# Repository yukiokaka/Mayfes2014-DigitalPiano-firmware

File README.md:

Mayfes2014-DigitalPiano-firmware
================================

This repository includes the firmware of DigitalPiano, made for mayfes 2014, EEIC the Universiy of Tokyo

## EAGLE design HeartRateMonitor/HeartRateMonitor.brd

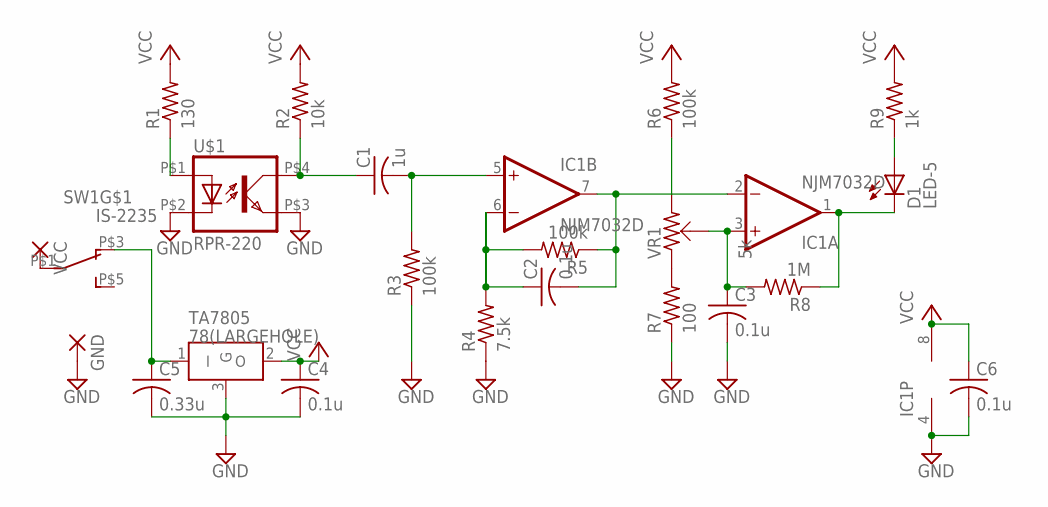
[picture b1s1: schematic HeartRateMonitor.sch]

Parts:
C1: 1u; C050-024X044
C2, C3, C4, C6: 0.1u; C050-024X044
C5: 0.33u; C050-024X044
D1: LED-5; LED5
GND: POWERPAD-2.4
IC1: NJM7032D; DIL08
R1: 130; 0207/10
R2: 10k; 0207/10
R3, R5, R6: 100k; 0207/10
R4: 7.5k; 0207/10
R7: 100; 0207/10
R8: 1M; 0207/10
R9: 1k; 0207/10
SW1: IS-2235
TA7805: 78(LARGEHOLE); 7805-LARGEHOLE
U$1: RPR-220
VCC: POWERPAD-2.4
VR1: 5k; VR-637A

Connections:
GND: C3.2, C4.2, C5.2, C6.2, GND.1, IC1.4 (V-), R3.1, R4.1, R7.1, TA7805.3 (G), U$1.P$2 (C), U$1.P$3 (EMIT)
unnamed: R1.1, U$1.P$1 (A)
unnamed: C1.1, R2.1, U$1.P$4 (COL)
unnamed: C1.2, IC1.5 (+IN), R3.2
unnamed: D1.A, R9.1
unnamed: C2.1, IC1.6 (-IN), R4.2, R5.2
unnamed: C2.2, IC1.2 (-IN), IC1.7 (OUT), R5.1
unnamed: R7.2, VR1.1
unnamed: R6.1, VR1.2
unnamed: C3.1, IC1.3 (+IN), R8.2, VR1.BR
unnamed: C5.1, SW1.P$3 (O), TA7805.1 (I)
unnamed: D1.K, IC1.1 (OUT), R8.1
unnamed: SW1.P$1, VCC.1
VCC: C4.1, C6.1, IC1.8 (V+), R1.2, R2.2, R6.2, R9.2, TA7805.2 (O)

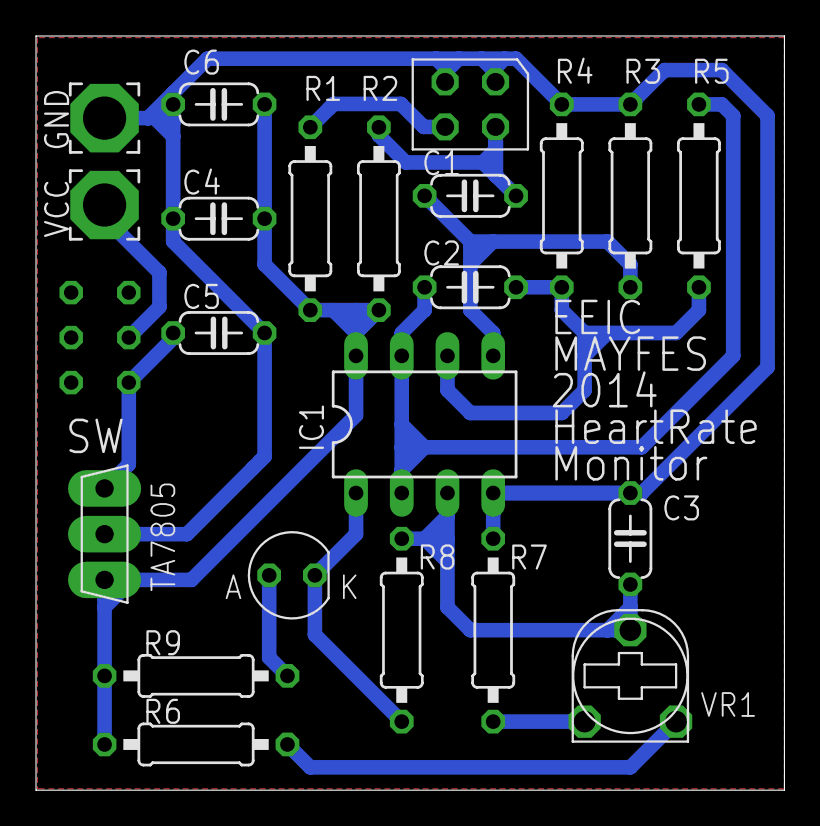
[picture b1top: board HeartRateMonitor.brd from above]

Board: 2 copper layers, 41.6 x 41.9 mm, 23 parts (0 on the bottom side), 14 nets.

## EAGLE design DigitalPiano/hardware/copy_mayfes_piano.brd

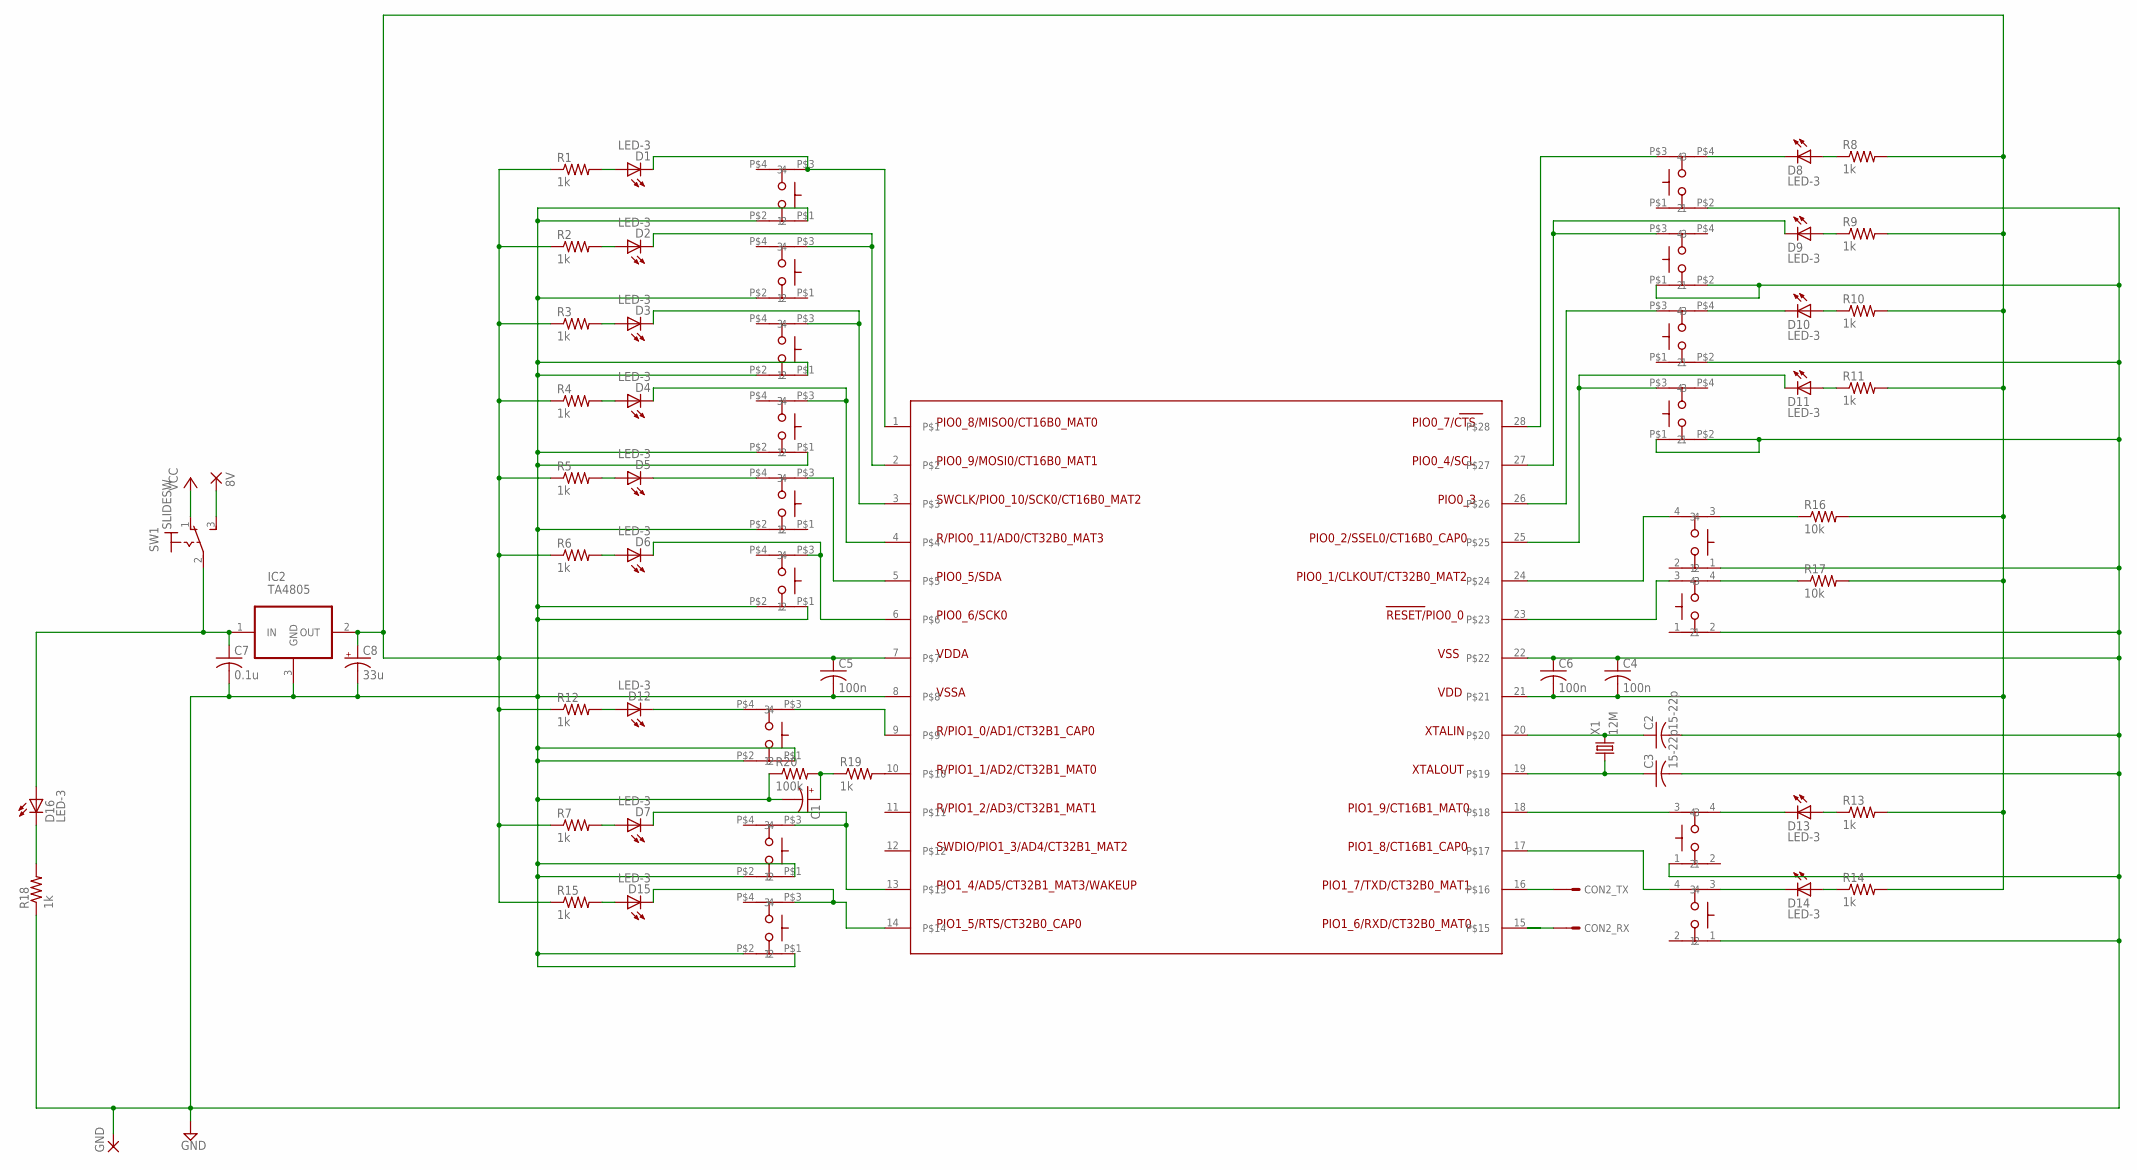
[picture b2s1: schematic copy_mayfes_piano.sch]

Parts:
8V: POWERPAD-2.0
BOOT: PUSHSW
C1: CC-5-13; E5-13
C2, C3: 15-22p; C050-024X044
C4, C5, C6: 100n; C050-024X044
C7: 0.1u; C050-024X044
C8: 33u; E2,5-5
CON2: UART-S; IL-G-04-S
D1, D2, D3, D4, D5, D6, D7, D8, D9, D10, D11, D12, D13, D14, D15, D16: LED-3; LED3
GND: POWERPAD-2.0
IC2: TA4805; HSIP3-P-254
PLAY: PUSHSW
R1, R2, R3, R4, R5, R6, R7, R8, R9, R10, R11, R12, R13, R14, R15, R18, R19: 1k; 0204/7
R16, R17: 10k; 0204/7
R20: 100k; 0204/7
REC: PUSHSW
RST: PUSHSW
SW1: SLIDESW
SW2, SW3, SW4, SW5, SW6, SW7, SW8, SW9, SW10, SW11, SW12, SW13, SW16: PUSHSW3; PUSHSE_BIG4
U$1: LPC1114FN28; DIP28(600MIL)
X1: 12M; HC49/S

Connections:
3.3V: C4.2, C5.1, C6.2, C8.+, IC2.2 (OUT), R1.1, R2.1, R3.1, R4.1, R5.1, R6.1, R7.1, R8.2, R9.2, R10.2, R11.2, R12.1, R13.2, R14.2, R15.1, R16.2, R17.2, U$1.7, U$1.21
8V: C7.1, D16.A, IC2.1 (IN), SW1.2
BUZZER: D7.K, SW8.P$3 (3), U$1.13
GND: BOOT.1, C1.-, C2.2, C3.2, C4.1, C5.2, C6.1, C7.2, C8.-, CON2.1 (GND), GND.1, IC2.3 (GND), PLAY.1, R18.1, R20.1, REC.1, RST.2, SW2.P$1 (1), SW2.P$2 (2), SW3.P$2 (2), SW4.P$1 (1), SW4.P$2 (2), SW5.P$1 (1), SW5.P$2 (2), SW6.P$2 (2), SW7.P$1 (1), SW7.P$2 (2), SW8.P$1 (1), SW8.P$2 (2), SW9.P$2 (2), SW10.P$1 (1), SW10.P$2 (2), SW11.P$2 (2), SW12.P$1 (1), SW12.P$2 (2), SW13.P$1 (1), SW13.P$2 (2), SW16.P$1 (1), SW16.P$2 (2), U$1.8, U$1.22
unnamed: D1.K, SW2.P$3 (3), U$1.1
unnamed: D1.A, R1.2
unnamed: R19.2, U$1.10
unnamed: D2.K, SW3.P$3 (3), U$1.2
unnamed: D2.A, R2.2
unnamed: D3.A, R3.2
unnamed: D4.A, R4.2
unnamed: D5.A, R5.2
unnamed: D6.A, R6.2
unnamed: D15.A, R15.2
unnamed: D5.K, SW6.P$4 (4)
unnamed: D12.A, R12.2
unnamed: D12.K, SW13.P$4 (4)
unnamed: D3.K, SW4.P$3 (3), U$1.3
unnamed: D4.K, SW5.P$3 (3), U$1.4
unnamed: SW6.P$3 (3), U$1.5
unnamed: D6.K, SW7.P$3 (3), U$1.6
unnamed: D15.K, SW16.P$3 (3), U$1.14
unnamed: SW9.P$3 (3), U$1.28
unnamed: D8.K, SW9.P$4 (4)
unnamed: D8.A, R8.1
unnamed: D9.A, R9.1
unnamed: D11.A, R11.1
unnamed: D10.A, R10.1
unnamed: D9.K, SW10.P$3 (3), U$1.27
unnamed: SW11.P$3 (3), U$1.26
unnamed: D11.K, SW12.P$3 (3), U$1.25
unnamed: D10.K, SW11.P$4 (4)
unnamed: D7.A, R7.2
unnamed: SW13.P$3 (3), U$1.9
unnamed: REC.3, U$1.18
unnamed: D14.K, PLAY.3
unnamed: D14.A, R14.1
unnamed: D13.A, R13.1
unnamed: PLAY.4, U$1.17
unnamed: D13.K, REC.4
unnamed: RST.3, U$1.23
unnamed: BOOT.3, R16.1
unnamed: BOOT.4, U$1.24
unnamed: R17.1, RST.4
unnamed: CON2.3 (S), U$1.16
unnamed: CON2.2 (S), U$1.15
unnamed: D16.K, R18.2
unnamed: C2.1, U$1.20, X1.2
unnamed: C3.1, U$1.19, X1.1
unnamed: C1.+, R19.1, R20.2
NAT: 8V.1, SW1.3 (S)
VCC: CON2.4 (VCC), SW1.1 (O)

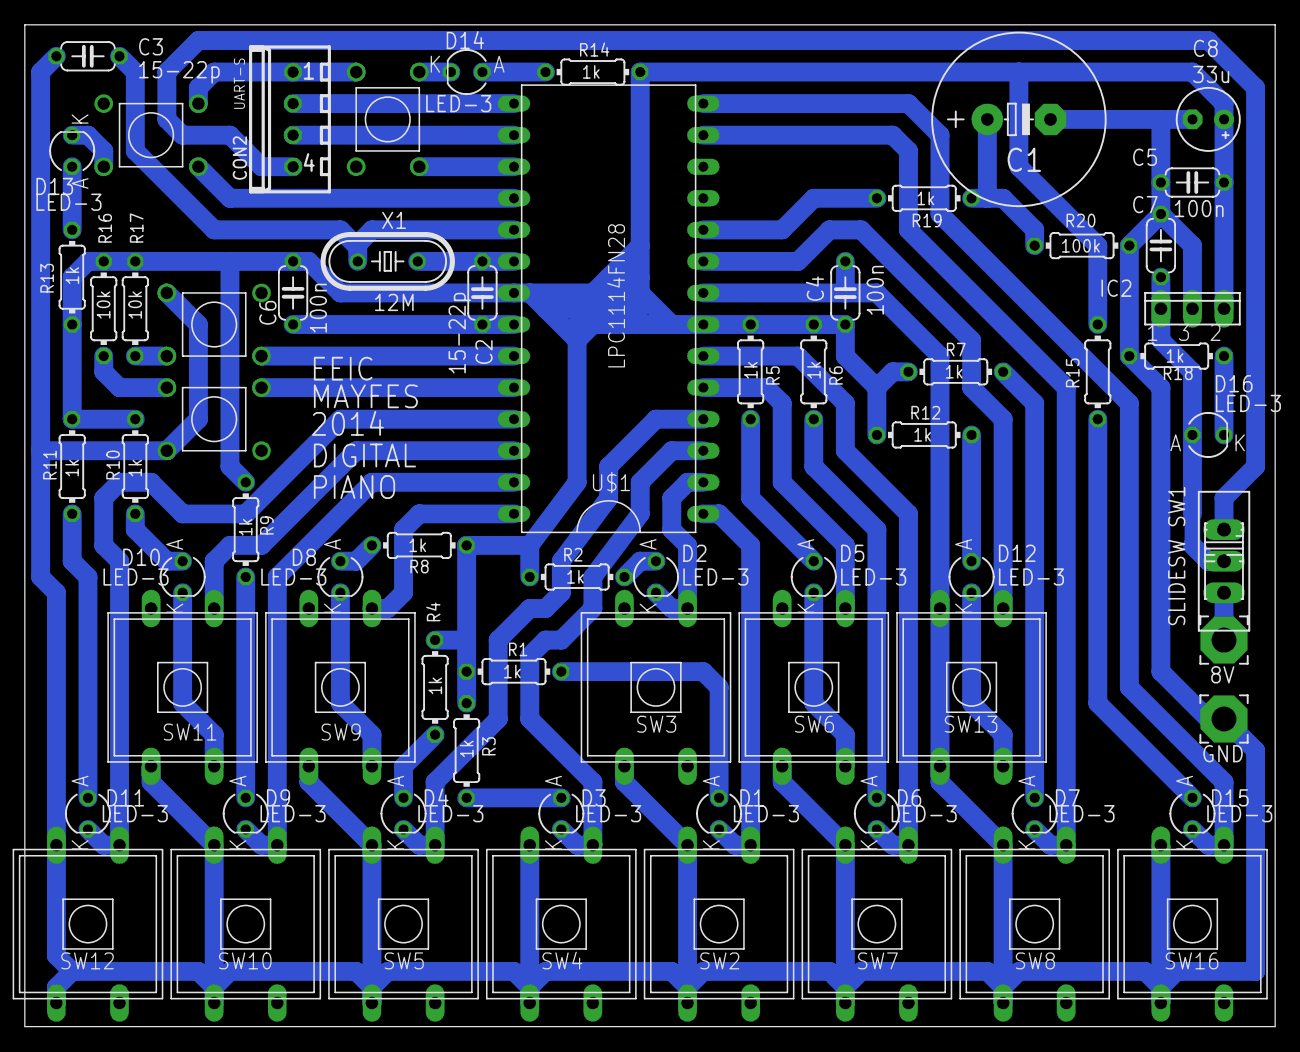
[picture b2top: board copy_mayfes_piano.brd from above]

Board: 2 copper layers, 100.6 x 80.6 mm, 68 parts (0 on the bottom side), 52 nets.

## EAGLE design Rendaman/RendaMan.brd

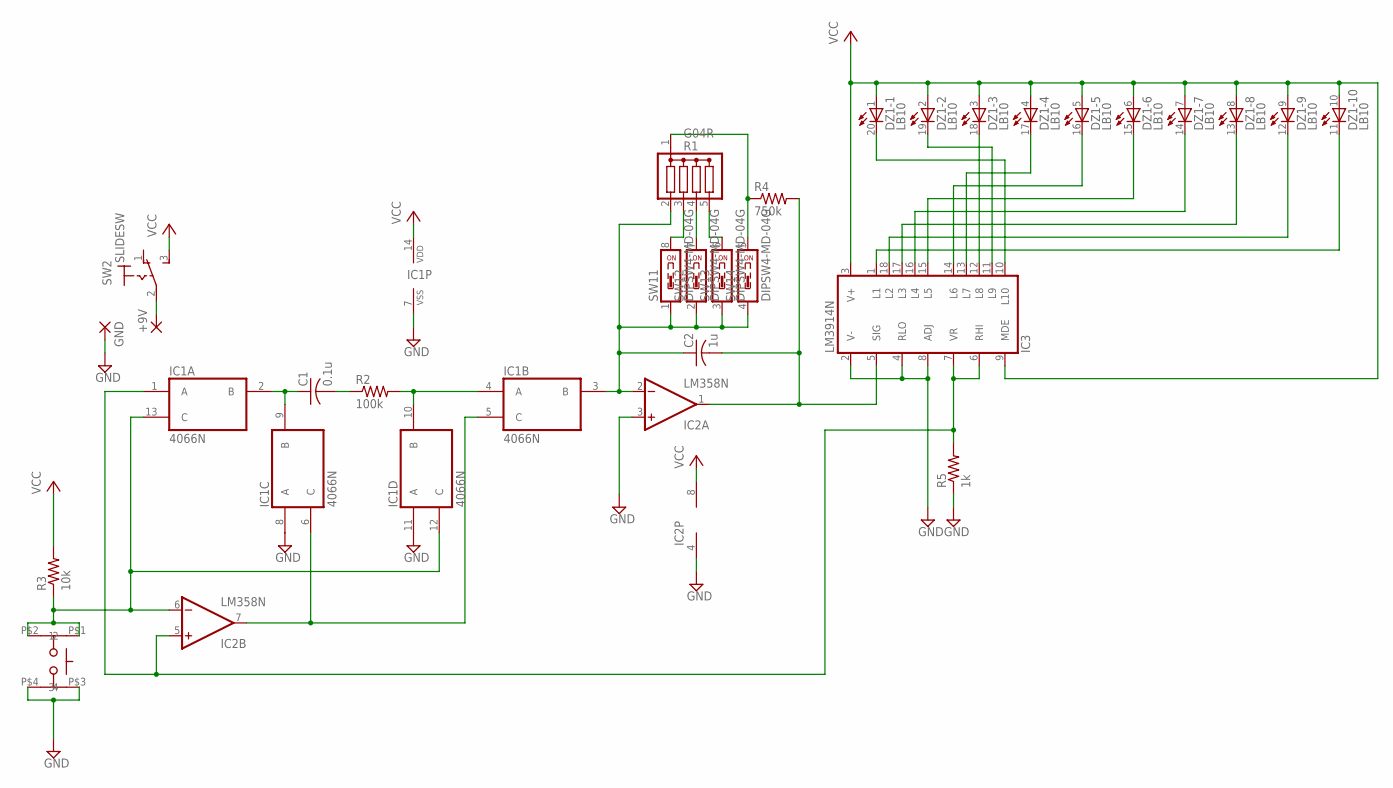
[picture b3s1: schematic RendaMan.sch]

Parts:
+9V: POWERPAD-2.4
C1: 0.1u; C050-024X044
C2: 1u; C050-024X044
DZ1: LB10
GND: POWERPAD-2.4
IC1: 4066N; DIL14
IC2: LM358N; DIL08
IC3: LM3914N; DIL18
R1: G04R; SIL5
R2: 100k; 0207/10
R3: 10k; 0207/10
R4: 750k; 0207/10
R5: 1k; 0207/10
SW1: DIPSW4-MD-04G; MD-04G
SW2: SLIDESW
SW4: PUSHSW3; PUSHSE_BIG4

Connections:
GND: GND.1, IC1.7 (VSS), IC1.8 (A), IC1.11 (A), IC2.3 (+IN), IC2.4 (V-), IC3.2 (V-), IC3.4 (RLO), IC3.8 (ADJ), R5.1, SW4.P$3 (3), SW4.P$4 (4)
unnamed: C1.1, IC1.2 (B), IC1.9 (B)
unnamed: C1.2, R2.1
unnamed: IC1.4 (A), IC1.10 (B), R2.2
unnamed: C2.1, IC1.3 (B), IC2.2 (-IN), R1.2, SW1.1, SW1.2 (1), SW1.3 (1), SW1.4 (1)
unnamed: R1.3, SW1.8 (2)
unnamed: R1.4, SW1.7 (2)
unnamed: R1.5, SW1.6 (2)
unnamed: R1.1, R4.1, SW1.5 (2)
unnamed: DZ1.17 (C), IC3.13 (L7)
unnamed: IC1.12 (C), IC1.13 (C), IC2.6 (-IN), R3.1, SW4.P$1 (1), SW4.P$2 (2)
unnamed: IC1.5 (C), IC1.6 (C), IC2.7 (OUT)
unnamed: C2.2, IC2.1 (OUT), IC3.5 (SIG), R4.2
unnamed: IC1.1 (A), IC2.5 (+IN), IC3.6 (RHI), IC3.7 (VR), R5.2
unnamed: DZ1.19 (C), IC3.11 (L9)
unnamed: DZ1.18 (C), IC3.12 (L8)
unnamed: DZ1.15 (C), IC3.15 (L5)
unnamed: DZ1.16 (C), IC3.14 (L6)
unnamed: DZ1.14 (C), IC3.16 (L4)
unnamed: DZ1.13 (C), IC3.17 (L3)
unnamed: DZ1.12 (C), IC3.18 (L2)
unnamed: DZ1.11 (C), IC3.1 (L1)
unnamed: +9V.1, SW2.2
unnamed: DZ1.20 (C), IC3.10 (L10)
VCC: DZ1.1 (A), DZ1.2 (A), DZ1.3 (A), DZ1.4 (A), DZ1.5 (A), DZ1.6 (A), DZ1.7 (A), DZ1.8 (A), DZ1.9 (A), DZ1.10 (A), IC1.14 (VDD), IC2.8 (V+), IC3.3 (V+), IC3.9 (MDE), R3.2, SW2.3 (S)

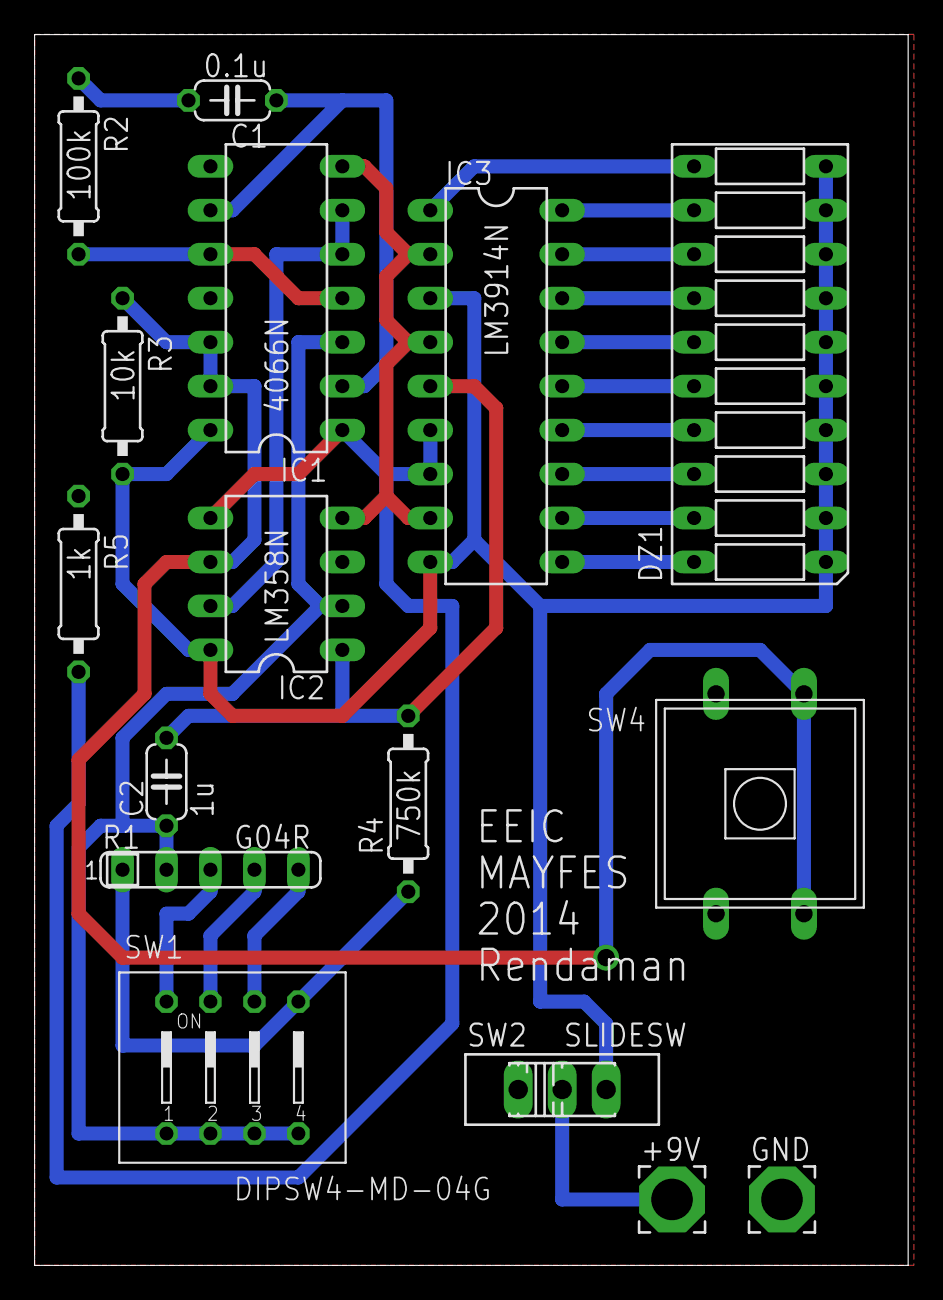
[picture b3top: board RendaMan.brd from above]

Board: 2 copper layers, 50.5 x 71.1 mm, 16 parts (0 on the bottom side), 25 nets.

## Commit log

2014-03-18 commit test
2014-03-19 ブザーとスイッチ個別での動作確認完了
2014-03-19 鍵盤を押したら音がなるようになった、ただ途中で止まるバグ有り
2014-03-20 録音中になり続けるバグ有り
2014-03-21 created Rendaman directory and added sch and brd files
2014-03-21 録音中の音が伸び続けるのを訂正。あとはブザーのバグだけ?
2014-03-26 止まるバグをごまかした
2014-03-31 modified pattern width
2014-03-31 added presentation for freshman
2014-04-02 modified wire witdth
2014-04-03 added switch
2014-04-03 modified TA7805 position in board data
2014-04-03 added silk
2014-04-03 add parts' names and circuit name
2014-04-03 modified symbol position for silk
2014-04-03 modified GERV data for silk
2014-04-03 made brd and sch data compatible with those in webdav
2014-04-03 added gerber data for fusionPCB
2014-04-04 RAMサイズを修正
2014-04-04 リンカスクリプトにあわせて修正
2014-04-04 音出す途中
2014-04-04 動作確認完了
2014-04-04 今度こそちゃんと動いたはず
2014-04-05 メインのリファクタリング(同時押しの仕様が変わった)
2014-04-05 さらに手直し
2014-04-05 フラッシュが怪しい
2014-04-05 フラッシュもうまく行った
2014-04-05 フラッシュを圧縮するようにした
2014-04-05 まだうまいこといかない
2014-04-24 録音がうまく行ってる
